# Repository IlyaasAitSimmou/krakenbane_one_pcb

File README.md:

# Krakenbane One — Rocketry DAQ Flight Computer

A data acquisition (DAQ) flight computer for a model rocket, designed for the Launch Canada competition. The system is two KiCad projects: a main flight computer board and a GNSS breakout that mounts separately and connects over a cable.

This is my first PCB design using SMT components, developed with support from university rocketry team members.

## Boards

|         | [DAQ-V4.1](DAQ-V4.1/) | [DAQ-GPS_Breakout-V1.0](DAQ-GPS_Breakout-V1.0/) |
| ------- | --------------------- | ----------------------------------------------- |
| Role    | Main flight computer  | GNSS receiver, mounted remotely                 |
| Outline | 38 × 100 mm           | 42 × 70 mm                                      |
| Stackup | 4-layer FR4, ~1.6 mm  | 4-layer FR4, ~1.6 mm                            |

The two boards are joined by a 6-pin JST GH (1.25 mm) cable carrying 3.3 V, GND, UART TX/RX, `TIMEPULSE`, and `NRESET`.

## Main board (DAQ-V4.1)

**MCU** — STM32F407VGT6 (Cortex-M4F, LQFP-100), 16 MHz crystal (NX3225GA), SWD debug on a 2×5 1.27 mm header with SWO.

**Sensors** — each on its own I²C bus, so there are no address collisions and each part can run at its full rate:

| Part          | Function                                | Range        |
| ------------- | --------------------------------------- | ------------ |
| LSM6DSV32X    | 6-axis IMU (accel + gyro), `INT` to MCU | ±32 g        |
| ADXL375       | High-g accelerometer                    | ±200 g       |
| MS5607-02BA03 | Barometric pressure / altitude          | 10–1200 mbar |

**Storage**

- microSD card (Hirose DM3BT push-pull socket) on **SPI1**, with 33 Ω series resistors on the clock and data lines, 4.7 kΩ bus pull-ups, and card-detect wired to `PE2`.
- W25Q64JV 64 Mbit NOR flash on **SPI2** for onboard logging independent of the card.

**Radio / telemetry** — XBee module on a 6-pin JST GH connector, driven from **USART2** with RTS/CTS hardware flow control.

**Power** — XT30 input at ~7.5 V → SS34 reverse-polarity diode → AP63203 synchronous buck to 3.3 V (SPM5030T 3.3 µH inductor). A separate `+3.3VA` analog rail is filtered from the digital rail through a ferrite bead for the MCU's analog supply. Power and status LEDs on board.

**Audio** — CMT-0502 magnetic buzzer switched by an AO3400A MOSFET with a B5819W flyback diode, for arming and continuity tones.

## GNSS breakout (DAQ-GPS_Breakout-V1.0)

u-blox SAM-M10Q with integrated patch antenna, broken out to a horizontal JST GH connector. Placed on its own board so the antenna can sit away from the flight computer's switching regulator and radio, with a clean ground plane underneath.

## Repository layout

```
DAQ-V4.1/                    Main flight computer
  DAQ-V4.1.kicad_sch/_pcb    Schematic and layout
  DAQ-V4.1.pdf               Schematic export
  DAQ-V4-*.pdf               Per-layer plots (copper, mask, paste, silkscreen, edge cuts)
  production/                Gerbers, BOM, pick-and-place, IPC netlist
  DRC.rpt / ERC.rpt          Latest design and electrical rule check reports
  *-backups/                 KiCad autosave history

DAQ-GPS_Breakout-V1.0/       GNSS breakout, same structure
```

Production files are generated with the KiCad Fabrication Toolkit and are formatted for JLCPCB assembly (`bom.csv` carries LCSC part numbers, `positions.csv` the placement data).

## Opening the project

Requires KiCad 8 or newer. Open `DAQ-V4.1/DAQ-V4.1.kicad_pro` or `DAQ-GPS_Breakout-V1.0/DAQ-GPS_Breakout-V1.0.kicad_pro`. Several footprints and 3D models come from project-local libraries, so open the project file rather than the `.kicad_pcb` directly.

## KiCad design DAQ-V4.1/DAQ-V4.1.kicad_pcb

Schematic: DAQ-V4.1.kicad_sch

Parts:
C1: 10 µF (0805); C_0805_2012Metric; LCSC Part # C162422
C3, C11, C13, C15, C18, C35: C (100 nF); C_0603_1608Metric; LCSC Part # C1591
C4: 100 nF; C_0603_1608Metric; LCSC Part # C127833
C5, C7: 2.2 µF; C_0603_1608Metric; LCSC Part # C913904
C9, C10, C12, C14, C19, C20, C21, C26, C29: 100 nF (0603); C_0603_1608Metric; LCSC Part # C1591
C16, C27, C31, C32: C (10 µF); C_0603_1608Metric; LCSC Part # C19702
C17, C24: 10 µF (0603); C_0603_1608Metric; LCSC Part # C19702
C22: 1 µF (0603); C_0603_1608Metric; LCSC Part # C15849
C23, C25: 0.1 µF (0603); C_0603_1608Metric; LCSC Part # C1591
C28: C (47 pF); C_0603_1608Metric; LCSC Part # C60302
C30: C (1 µF); C_0603_1608Metric; LCSC Part # C15849
C57, C58: 10 pF (0603); C_0603_1608Metric; LCSC Part # C1634
COUT1, COUT2: 22 µF (0805); C_0805_2012Metric; LCSC Part # C86816
D1: LED; LED_0603_1608Metric; LCSC Part # C2287
D2: SS34; D_SMA; LCSC Part # C8678
D3: B5819W SL; D_SOD-123; LCSC Part # C8598
FB1: FCM1608KF-601T03; L_0603_1608Metric; LCSC Part # C141723
H1, H2, H3, H4, H5, H6: MountingHole; MountingHole_2.2mm_M2
IC1: W25Q64JVSSIQ; SOIC127P790X216-8N; Mouser Part Number 454-W25Q64JVSSIQ
J1: GNSS Connector - PCB; JST_GH_BM06B-GHS-TBT_1x06-1MP_P1.25mm_Vertical
J2: Conn_02x05_Odd_Even; PinHeader_2x05_P1.27mm_Vertical_SMD; LCSC Part # C5160761
J3: XBEE Connector; JST_GH_BM06B-GHS-TBT_1x06-1MP_P1.25mm_Vertical
J4: DM3BT-DSF-PEJS; HRS_DM3BT-DSF-PEJS; LCSC Part # C597972
J5: Conn_01x02; AMASS_XT30UPB-M_1x02_P5.0mm_Vertical; LCSC Part # C428721
L1: SPM5030T-3R3M-HZ; IND_SPM5030T-3R3M-HZ; PARTREV 20210423; LCSC Part # C518955
LS2: CMT-0502-75-SMT-TR; XDCR_CMT-0502-75-SMT-TR; PARTREV 1.0; DigiKey_Part_Number 102-CMT-0502-75-SMT-CT-ND
Power_On_LED1: RED; LED_0603_1608Metric; LCSC Part # C2286
Q1: AO3400A; SOT95P280X125-3N; PARTREV L; LCSC Part # C20917
R7: R (300 Ω); R_0603_1608Metric; LCSC Part # C23025
R(PULL)1, R(PULL)2, R(PULL)15, R(PULL)16, R(PULL)18, R(PULL)19: R (4.7 kΩ); R_0603_1608Metric; LCSC Part # C23046
R(PULL)3, R(PULL)4: R (10 kΩ); R_0603_1608Metric; LCSC Part # C22790
R(PULL)9: R (300 Ω); R_0603_1608Metric; LCSC Part # C23025
R(T)1: R (100 Ω); R_0603_1608Metric; LCSC Part # C22775
R(T)2: R (10 kΩ); R_0603_1608Metric; LCSC Part # C22790
R_Pull_Flash_1: 10 kΩ; R_0603_1608Metric; LCSC Part # C22790
R_Pull_MicroSD_1, R_Pull_MicroSD_2, R_Pull_MicroSD_3, R_Pull_MicroSD_4, R_Pull_MicroSD_5, R_Pull_MicroSD_6: 4.7 kΩ; R_0603_1608Metric; LCSC Part # C23046
R_Series_MicroSD_1, R_Series_MicroSD_2, R_Series_MicroSD_3: 33 Ω; R_0603_1608Metric; LCSC Part # C23140
U2: LSM6DSV32XTR; LGA-14L_2p5X3p0X0p86_STM; LCSC C22461202
U4: ADXL375BCCZ; LGA_CC-14-1_ADI; LCSC Part # C579466
U5: MS560702BA03-50; SON125P300X500X100-8N; LCSC Part # C97627
U7: STM32F407VGTx; LQFP-100_14x14mm_P0.5mm; LCSC Part # C12345
U9: AP63203WU; TSOT-23-6; LCSC Part # C780769
XTAL1: NX3225GA-16.000M-STD-CRG-2; NX3225GA-16.000M-STD-CRG-2_NDK; LCSC Part # C156247

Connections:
+3.3V: C3.2, C9.1, C10.1, C11.1, C12.1, C13.2, C14.1, C15.2, C16.2, C17.1, C18.2, C19.1, C20.1, C23.2, C24.2, C25.2, C26.1, C27.2, C28.2, C30.2, C31.2, C32.1, COUT1.1, COUT2.1, D3.1 (K), FB1.2, IC1.3 (~WP_(IO2)), IC1.7 (~HOLD_OR_/RESET_(IO3)), IC1.8 (VCC), J1.1, J2.1, J3.1, J4.4 (VDD), L1.2, LS2.P, Power_On_LED1.2 (A), R(PULL)1.1, R(PULL)2.1, R(PULL)3.2, R(PULL)15.1, R(PULL)16.1, R(PULL)18.1, R(PULL)19.1, R_Pull_Flash_1.1, R_Pull_MicroSD_1.2, R_Pull_MicroSD_2.2, R_Pull_MicroSD_3.2, R_Pull_MicroSD_4.2, R_Pull_MicroSD_5.2, R_Pull_MicroSD_6.1, U2.5 (VDD_IO), U2.8 (VDD), U2.10 (OCS_AUX), U2.11 (SDO_AUX), U2.12 (CS), U4.1 (VDD_I/O), U4.6 (VS), U4.7 (*CS), U4.12 (SDO/ALT_ADDRESS), U5.1 (VDD), U5.2 (PS), U7.6 (VBAT), U7.11 (VDD), U7.19 (VDD), U7.28 (VDD), U7.50 (VDD), U7.75 (VDD), U7.100 (VDD), U9.1 (FB)
+3.3VA: C21.1, C22.1, C35.1, FB1.1, U7.21 (VREF+), U7.22 (VDDA)
+7.5V: D2.2 (A), J5.2
/ADXL375 SCL: R(PULL)19.2, U4.14 (SCL/SCLK), U7.67 (PA8)
/ADXL375 SDA: R(PULL)18.2, U4.13 (SDA/SDI/SDIO), U7.66 (PC9)
/BOOT0: R(PULL)4.1, U7.94 (BOOT0)
/LSM6DSV INT: U2.4 (INT1), U7.90 (PB4)
/LSM6DSV SCL: R(PULL)1.2, U2.13 (SCL), U7.92 (PB6)
/LSM6DSV SDA: R(PULL)2.2, U2.14 (SDA), U7.93 (PB7)
/MS5607 SCL: R(PULL)15.2, U5.8 (SCLK), U7.47 (PB10)
/MS5607 SDA: R(PULL)16.2, U5.7 (SDI/SDA), U7.48 (PB11)
/NRST: C29.2, J2.10, R(PULL)3.1, U7.14 (NRST)
/PE2: J4.SW-A, R_Pull_MicroSD_6.2, U7.1 (PE2)
/PWR_LED_K: Power_On_LED1.1 (K), R(PULL)9.2
/SAM-M10Q NRESET: J1.6, U7.87 (PD6)
/SAM-M10Q RX: J1.3, U7.23 (PA0)
/SAM-M10Q TIMEPULSE: J1.5, U7.86 (PD5)
/SAM-M10Q TX: J1.4, U7.24 (PA1)
/SPI1_MISO: J4.7 (DAT0), R_Pull_MicroSD_1.1, R_Series_MicroSD_2.1
/SPI1_MOSI: J4.3 (CMD), R_Pull_MicroSD_2.1, R_Series_MicroSD_3.1
/SPI1_NSS: J4.2 (DAT3/CD), R_Pull_MicroSD_3.1, U7.29 (PA4)
/SPI1_SCK: J4.5 (CLK), R_Series_MicroSD_1.1
/SPI2_MISO: IC1.2 (DO_(IO1)), U7.53 (PB14)
/SPI2_MOSI: IC1.5 (DI_(IO0)), U7.54 (PB15)
/SPI2_NSS: IC1.1 (~CS), R_Pull_Flash_1.2, U7.51 (PB12)
/SPI2_SCK: IC1.6 (CLK), U7.52 (PB13)
/SWCLK: J2.4, U7.76 (PA14)
/SWDIO: J2.2, U7.72 (PA13)
/SWO: J2.6, U7.89 (PB3)
/USART2_CTS: J3.4, U7.84 (PD3)
/USART2_RTS: J3.5, U7.85 (PD4)
/USART2_RX: J3.3, U7.26 (PA3)
/USART2_TX: J3.2, U7.25 (PA2)
GND: C1.2, C3.1, C5.1, C7.1, C9.2, C10.2, C11.2, C12.2, C13.1, C14.2, C15.1, C16.1, C17.2, C18.1, C19.2, C20.2, C21.2, C22.2, C23.1, C24.1, C25.1, C26.2, C27.1, C28.1, C29.1, C30.1, C31.1, C32.2, C35.2, C57.1, C58.1, COUT1.2, COUT2.2, D1.1 (K), IC1.4 (GND), J1.2, J2.3, J2.5, J2.9, J3.6, J4.6 (VSS), J4.S1 (SHIELD), J4.S2 (SHIELD), J4.S3 (SHIELD), J4.S4 (SHIELD), J4.SW-B, J5.1, Q1.2, R(PULL)4.2, R(PULL)9.1, R(T)2.2, U2.1 (SDO/SA0), U2.2 (SDX/AH1/QVAR1), U2.3 (SCX/AH2/QVAR2), U2.6 (GND), U2.7 (GND), U4.2 (GND), U4.4 (GND), U4.5 (GND), U5.3 (GND), U5.4 (~CSB), U5.5 (~CSB), U7.10 (VSS), U7.20 (VSSA), U7.27 (VSS), U7.74 (VSS), U7.99 (VSS), U9.4 (GND), XTAL1.2, XTAL1.4
unnamed: D1.2 (A), R7.2
unnamed: C1.1, D2.1 (K), U9.2 (EN), U9.3 (IN)
unnamed: D3.2 (A), LS2.N, Q1.3
unnamed: J4.8 (DAT1), R_Pull_MicroSD_5.1
unnamed: J4.1 (DAT2), R_Pull_MicroSD_4.1
unnamed: Q1.1, R(T)1.1, R(T)2.1
unnamed: R_Series_MicroSD_1.2, U7.30 (PA5)
unnamed: R_Series_MicroSD_2.2, U7.31 (PA6)
unnamed: R_Series_MicroSD_3.2, U7.32 (PA7)
unnamed: R7.1, U7.39 (PE8)
unnamed: R(T)1.2, U7.40 (PE9)
unnamed: C57.2, U7.12 (PH0), XTAL1.1
unnamed: C58.2, U7.13 (PH1), XTAL1.3
unnamed: C5.2, U7.49 (VCAP_1)
unnamed: C7.2, U7.73 (VCAP_2)
unnamed: C4.1, U9.6 (BST)
unnamed: C4.2, L1.1, U9.5 (SW)

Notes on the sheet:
MOUNTING HOLES
JTAG/SWD PINS
MS5607 - BAROMETRIC PRESSURE SENSOR
LSM6DSV32 - 6-AXIS INERTIAL MEASUREMENT UNIT
STM32F407 - MICROCONTROLLER
MAIN BOARD
JST-GH GNSS CONNECTORS
SENSOR SUITE
SAM-M10Q - GNSS MODULE
ADXL375 - HIGH G ACCELEROMETER
XBEE CONNECTOR
DM3BT-DSF-PEJS - MICROSD CONNECTOR
GNSS BOARD
GNSS
DATA STORAGE
W25Q64 - FLASH CHIP
XT30 CONNECTORS
BUCK CONVERTER
AP63203 - BUCK SWITCHING REGULATOR

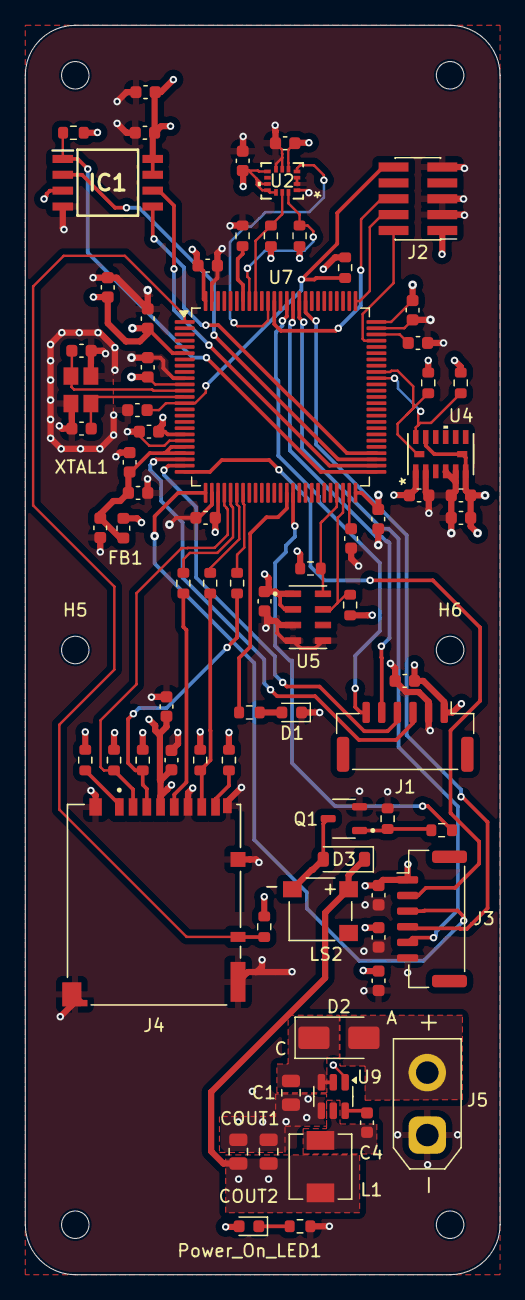
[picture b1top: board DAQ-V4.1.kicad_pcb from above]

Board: 4 copper layers, 38.0 x 100.0 mm, 82 parts (0 on the bottom side), 51 nets.

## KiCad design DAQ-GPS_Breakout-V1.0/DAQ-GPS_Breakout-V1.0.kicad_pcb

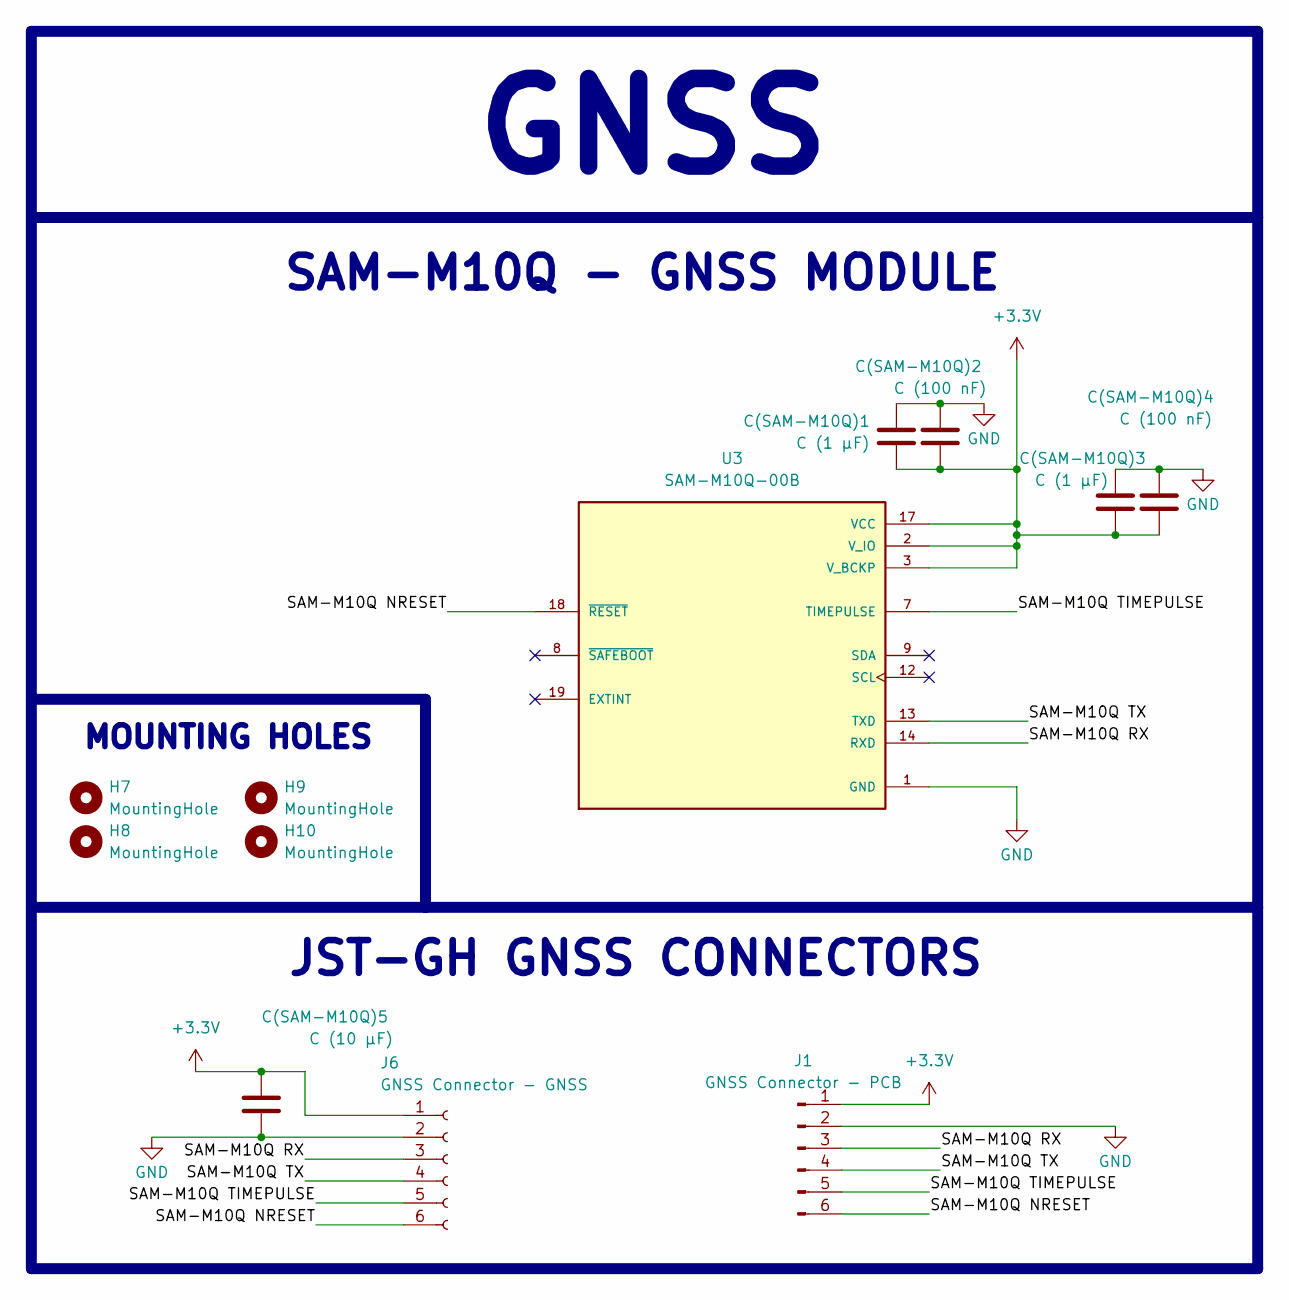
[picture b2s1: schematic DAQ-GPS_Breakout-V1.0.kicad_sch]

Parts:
C(SAM-M10Q)1, C(SAM-M10Q)3: C (1 µF); C_0603_1608Metric
C(SAM-M10Q)2, C(SAM-M10Q)4: C (100 nF); C_0603_1608Metric
C(SAM-M10Q)5: C (10 µF); C_0603_1608Metric
H7, H8, H9, H10: MountingHole; MountingHole_2.2mm_M2
J1: GNSS Connector - PCB; JST_GH_BM06B-GHS-TBT_1x06-1MP_P1.25mm_Vertical
J6: GNSS Connector - GNSS; JST_GH_SM06B-GHS-TB_1x06-1MP_P1.25mm_Horizontal
U3: SAM-M10Q-00B; XCVR_SAM-M10Q-00B; PARTREV R03

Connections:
+3.3V: C(SAM-M10Q)1.2, C(SAM-M10Q)2.2, C(SAM-M10Q)3.2, C(SAM-M10Q)4.2, C(SAM-M10Q)5.1, J1.1, J6.1, U3.2 (V_IO), U3.3 (V_BCKP), U3.17 (VCC)
/SAM-M10Q NRESET: J1.6, J6.6, U3.18 (~RESET)
/SAM-M10Q RX: J1.3, J6.3, U3.14 (RXD)
/SAM-M10Q TIMEPULSE: J1.5, J6.5, U3.7 (TIMEPULSE)
/SAM-M10Q TX: J1.4, J6.4, U3.13 (TXD)
GND: C(SAM-M10Q)1.1, C(SAM-M10Q)2.1, C(SAM-M10Q)3.1, C(SAM-M10Q)4.1, C(SAM-M10Q)5.2, J1.2, J6.2, U3.1 (GND), U3.4 (GND), U3.5 (GND), U3.6 (GND), U3.10 (GND), U3.11 (GND), U3.15 (GND), U3.16 (GND), U3.20 (GND)

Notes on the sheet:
MOUNTING HOLES
GNSS
JST-GH GNSS CONNECTORS
SAM-M10Q - GNSS MODULE

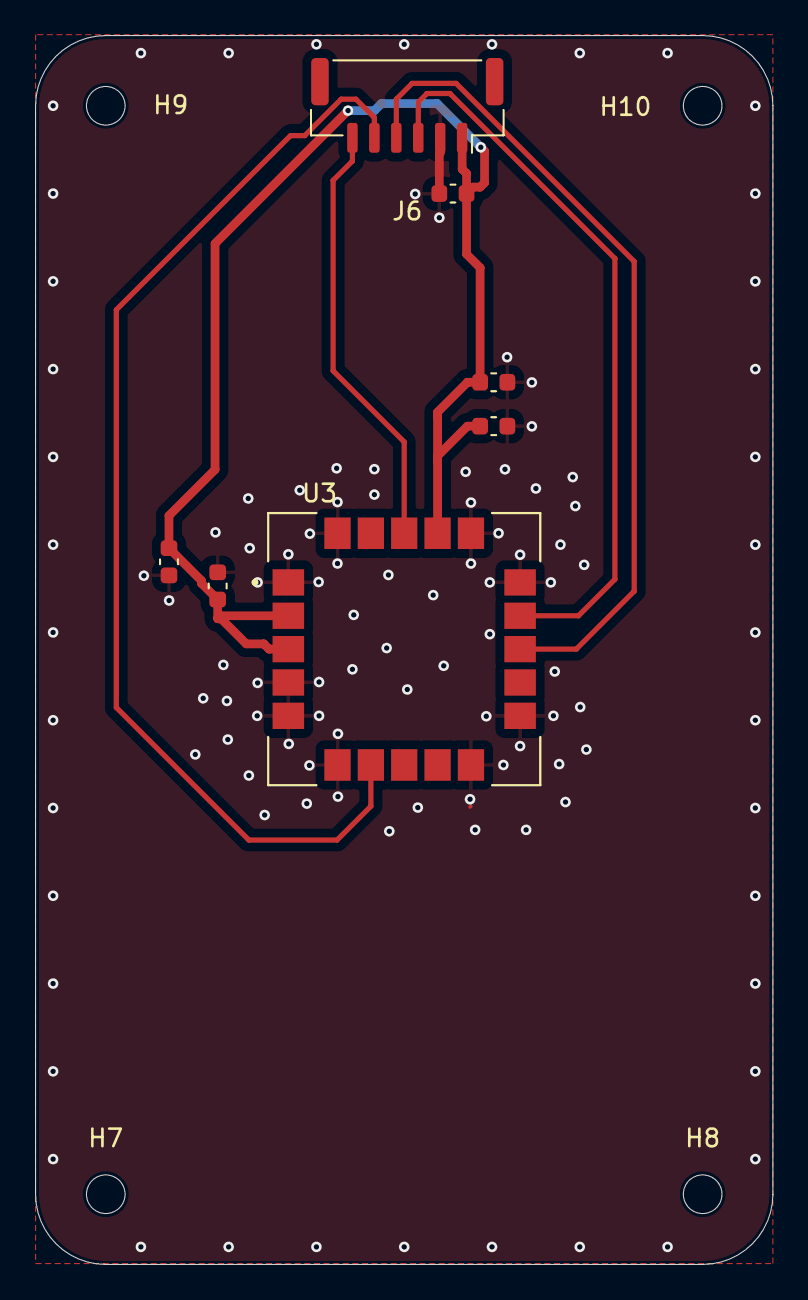
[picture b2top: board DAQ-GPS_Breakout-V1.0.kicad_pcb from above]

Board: 4 copper layers, 42.0 x 70.0 mm, 11 parts (0 on the bottom side), 6 nets.

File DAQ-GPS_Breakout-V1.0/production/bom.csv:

Designator,Footprint,Quantity,Value,LCSC Part #
"C(SAM-M10Q)1, C(SAM-M10Q)3",0603,2,C (1 µF),
"C(SAM-M10Q)2, C(SAM-M10Q)4",0603,2,C (100 nF),
C(SAM-M10Q)5,0603,1,C (10 µF),
J6,JST_GH_SM06B-GHS-TB_1x06-1MP_P1.25mm_Horizontal,1,GNSS Connector - GNSS,
U3,XCVR_SAM-M10Q-00B,1,SAM-M10Q-00B,
